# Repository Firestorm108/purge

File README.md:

# purge
**Purge** is a fully open source wireless inductively coupled plasma cleaner consisting of three isolated PCBs; the external user-control board, STM32 based motherboard, spark generator/ICP driver, and a vaccum chamber.

# PCB & Assembly

# The Process

**Purge** is a specialized type of plasma cleaner. There are **zero** electrodes in the vacuum chamber, meaning the sterility levels are very high, atomically sterile even. There are three stages to the process.

<h3>Stage 1: Chamber Prep</h3>
A 4.5 CFM standard vacuum pump evacuates much of the air inside of the glass dome to 37.5 mTorr. This makes the plasma much easier to form, as there is a reduced gas density. 
The chamber is made up of a custom machined aluminum base and a cheap glass dome you can find on Amazon. There is a slight implosion risk, so it is important you wear proper PPE.

<h3>Stage 2: Plasma Formation</h3>
There are two parts to the plasma formation. Since inductively coupled plasma (ICP) is relatively harder to form than capacitively coupled plasma or direct discharges, simply running the RF through the primary coil may not form the plasma.
To form the plasma, we initiate a short high voltage spark with an external device. In this case, I'm using a high frequency solid state plasma flame generator, similar to the ICP circuit itself. It ionizes some of the gas in the chamber, making
ICP form much easier. The ICP driver powers on after this, and the chamber fills with plasma.

<h3>Stage 3: Adjustment & Control</h3>
You can change the plasma inside the chamber using the built in STM32 interrupter. It allows you to pulse the plasma at any desired frequency within the chip and MOSFETs limits. This can be useful if you are trying to 
do research using the device, or wish to adjust power levels based on the item you are sterilizing.

# Bill of Materials

| Item | Price | Link |
|---|---:|---|
| Control PCB | $10 | JLCPCB |
| Header Pins | $3 | [AliExpress](https://www.aliexpress.us/item/3256801327743339.html) |
| OLED Screen | $4 | [AliExpress](https://www.aliexpress.us/item/3256805954920554.html) |
| 10K Potentiometers | $4 | [AliExpress](https://www.aliexpress.us/item/3256809938132755.html) |
| Push Button | $4 | [AliExpress](https://www.aliexpress.us/item/3256808590713102.html) |
| 3mm Flat Top LEDs | $2 | [AliExpress](https://www.aliexpress.us/item/2251801539552759.html) |
| F-F Jumpers | $2 | [AliExpress](https://www.aliexpress.us/item/2255800018543465.html) |
| ICP Driver PCB + Assembly | $55 | JLCPCB |
| FQA18N50 MOSFETs | $10 | [AliExpress](https://www.aliexpress.us/item/3256811881586105.html) |
| 6kV 33pF Capacitors | $2 | [AliExpress](https://www.aliexpress.us/item/2251832494176278.html) |
| 12AWG Solid Core | $4 | [AliExpress](https://www.aliexpress.us/item/3256808900976117.html) |
| Massive Heatsink | $10 | [AliExpress](https://www.aliexpress.us/item/3256809168389115.html) |
| HFSSTC Module | $24 | [AliExpress](https://www.aliexpress.us/item/3256810369157220.html) |
| 24AWG Solid Core (Inductor Wire) | $7 | [Amazon](https://www.amazon.com/0-2mm%C2%B2-Electrical-Colors-Tinned-breadboard/dp/B09WMQZYXV/) |
| 6AWG Primary Copper | $24 | [Amazon](https://www.amazon.com/99-9-Copper-Diameter-Jewelry-Making/dp/B0CNRT19WB/) |
| Purge Motherboard PCB + Assembly | $80 | JLCPCB |
| 24V → 12V Isolation SMPS | $6 | [AliExpress](https://www.aliexpress.us/item/3256807230654430.html) |
| 24V 10A Power Supply | $30 | [Amazon](https://www.amazon.com/Power-Supply-Adapter-Transformers-Universal/dp/B0D5B33JCH) |
| JLCPCB Customs & Shipping | $91 | JLCPCB |
| 4" × 7" Glass Dome | $30 | [Amazon](https://www.amazon.com/Plymor-Brand-Glass-Display-Cloche/dp/B006XIQGX8/) |
| 4.5 CFM Vacuum Pump | $60 | [Amazon](https://www.amazon.com/VECOTOOLS-Foldable-Automotive-Household-Maintenance/dp/B0GZVLP3PL/) |
| Hosing & Gauge | $28 | [Amazon](https://www.amazon.com/R410A-Recharge-Manifold-Gauge-Set/dp/B0DZ6G6ZBT/) |
| SAE to NPT Adapter | $9 | [Amazon](https://www.amazon.com/uxcell-Fitting-Connector-Conditioner-Refrigeration/dp/B08MZ4TPMZ/) |
| NPT Tap | $7 | [Amazon](https://www.amazon.com/Drill-America-DWTPT1-Qualtech-Carbon/dp/B01DZD1SSQ/) |
| M5 × 100mm Threaded Rods | $10 | [Amazon](https://www.amazon.com/LWCUSNJ-Threaded-M5-0-8mm-Stainless-Threads/dp/B0FHB8P689/) |
| Silicone Caulk | $3 | [Amazon](https://www.amazon.com/White-Acrylic-Latex-Caulk-Silicone/dp/B00GVLHBDG/) |
| Custom Aluminum Base Plate | $50 | JLC CNC |
| Silicone Isolation Feet | $20 | [Amazon](https://www.amazon.com/Isolation-Feet-8Pack-Turntable-Subwoofer-Resonance/dp/B0FX8S3D77) |

**Total: $589**

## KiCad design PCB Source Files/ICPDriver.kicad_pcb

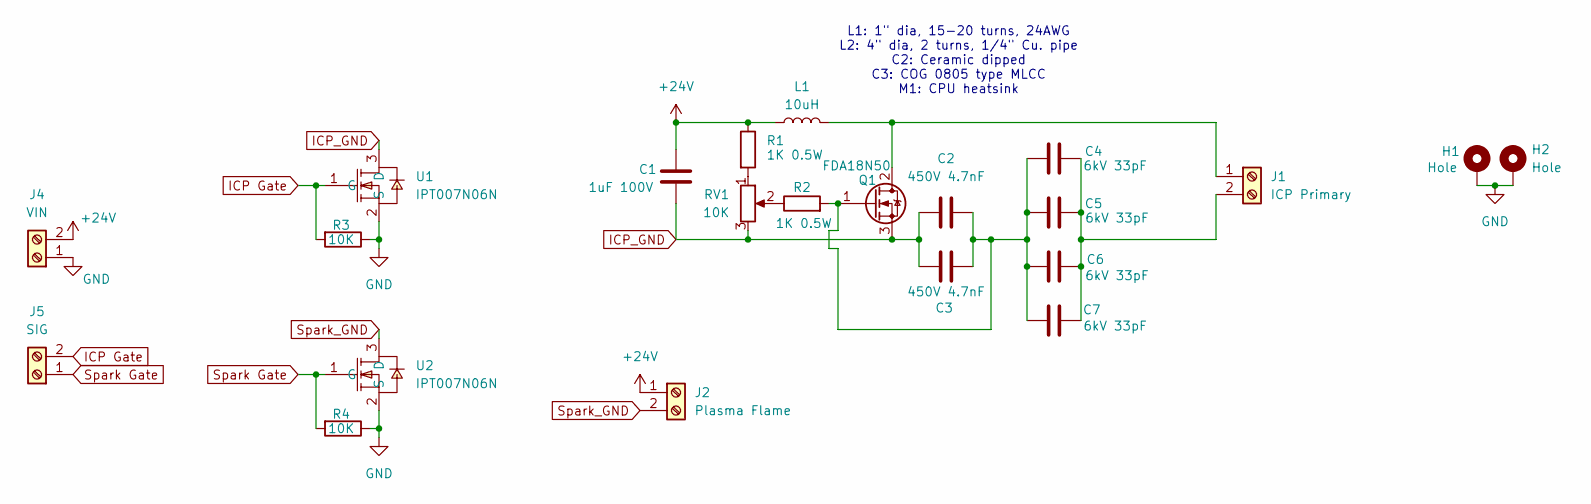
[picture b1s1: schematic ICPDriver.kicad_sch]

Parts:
C1: 1uF 100V; C_1206_3216Metric
C2, C3: 450V 4.7nF; C_1812_4532Metric
C4, C5, C6, C7: 6kV 33pF; C_Disc_D7.5mm_W5.0mm_P7.50mm
H1, H2: Hole; MountingHole_3.2mm_M3_Pad
J1: ICP Primary; CONN-TH_P10.16_KF135T-10.16-2P
J2: Plasma Flame; CONN-TH_P10.16_KF135T-10.16-2P
J4: VIN; CONN-TH_P10.16_KF135T-10.16-2P
J5: SIG; CONN-TH_P10.16_KF135T-10.16-2P
L1: 10uH; CONN-TH_P10.16_KF135T-10.16-2P
Q1: FDA18N50; TO-247-3_Vertical
R1, R2: 1K 0.5W; R_2512_6332Metric
R3, R4: 10K; R_0603_1608Metric
RV1: 10K; RES-ADJ-TH_RK1631110U1Q
U1, U2: IPT007N06N; HSOF-8_IPT007N06N; MPN IPT007N06N(TOKMAS); LCSC Part C19626228

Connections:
+24V: C1.1, J2.1, J4.2, L1.1, R1.1
GND: H1.1 (1_1), H2.1 (1_1), J4.1, R3.1, R4.1, U1.2 (S), U2.2 (S)
ICP Gate: J5.2, R3.2, U1.1 (G)
ICP_GND: C1.2, C2.1, C3.1, Q1.3 (S), RV1.3, U1.3 (D)
unnamed: J1.1, L1.2, Q1.2 (D)
unnamed: C4.2, C5.2, C6.2, C7.2, J1.2
unnamed: C2.2, C3.2, C4.1, C5.1, C6.1, C7.1, Q1.1 (G), R2.2
unnamed: R1.2, RV1.1
unnamed: R2.1, RV1.2
Spark Gate: J5.1, R4.2, U2.1 (G)
Spark_GND: J2.2, U2.3 (D)

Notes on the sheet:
L1: 1" dia, 15-20 turns, 24AWG L2: 4" dia, 2 turns, 1/4" Cu. pipe C2: Ceramic dipped C3: COG 0805 type MLCC M1: CPU heatsink

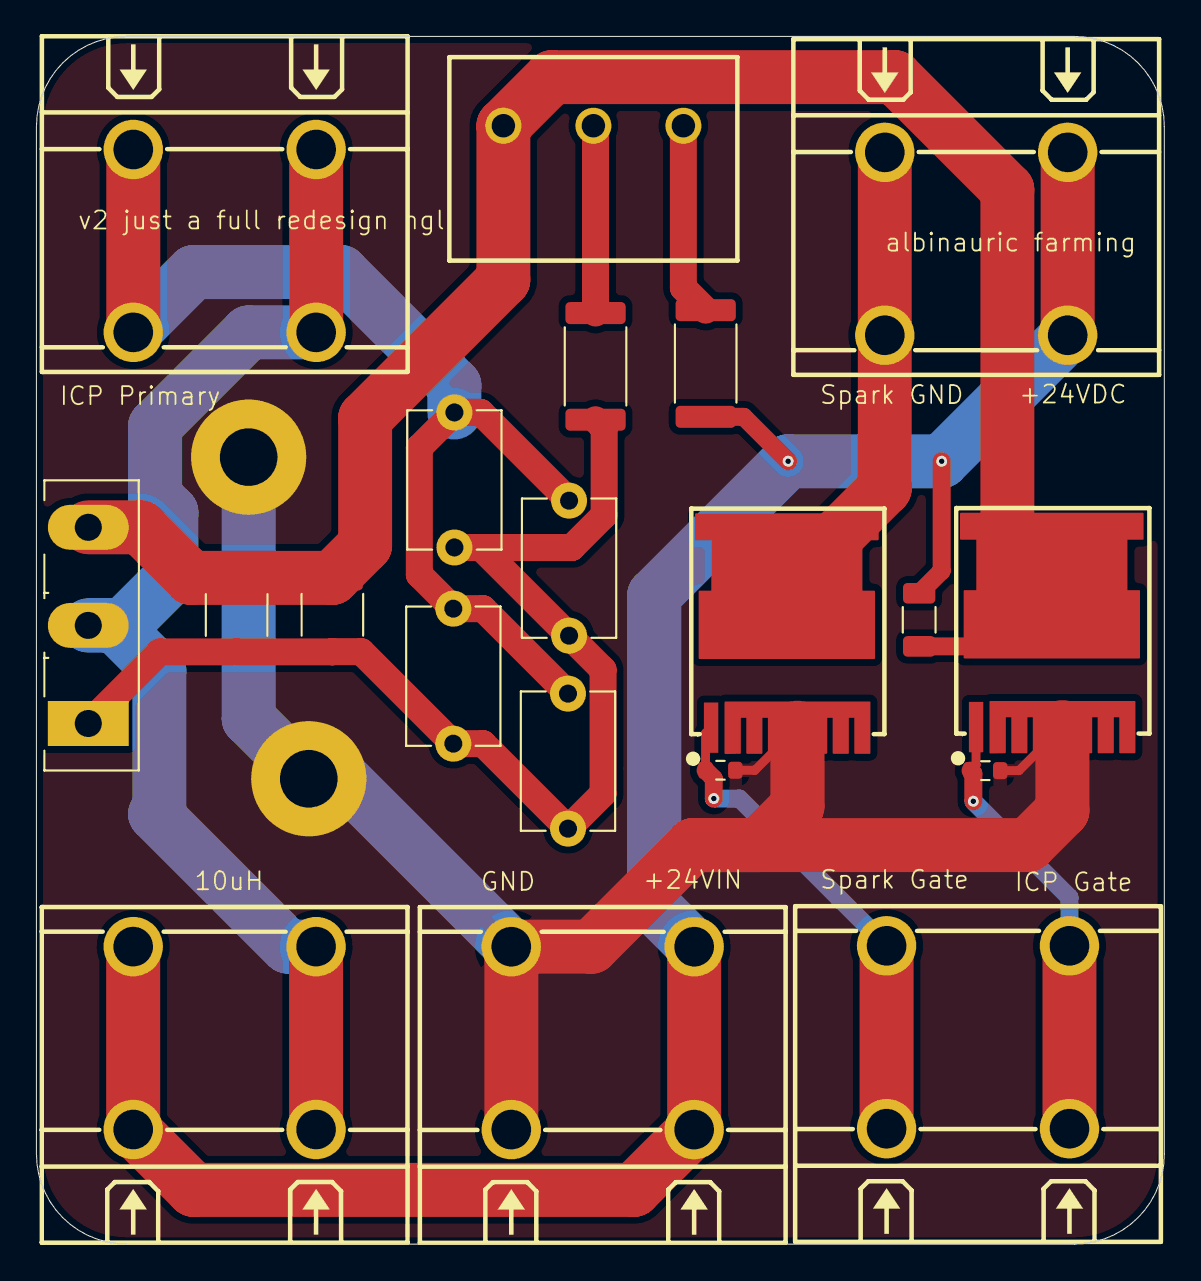
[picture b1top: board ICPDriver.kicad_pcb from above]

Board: 2 copper layers, 62.7 x 67.1 mm, 22 parts (0 on the bottom side), 11 nets.

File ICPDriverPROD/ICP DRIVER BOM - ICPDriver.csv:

Id,Designator,Footprint,Quantity,Comment,Supplier and ref
1,C1,C_1206_3216Metric,1,1uF 100V,
2,"C2, C3",C_1812_4532Metric,2,450V 4.7nF,
3,"C4, C5, C6, C7",C_Disc_D7.5mm_W5.0mm_P7.50mm,4,6kV 33pF,
4,J1,CONN-TH_P10.16_KF135T-10.16-2P,1,ICP Primary,
5,J2,CONN-TH_P10.16_KF135T-10.16-2P,1,Plasma Flame,
6,J4,CONN-TH_P10.16_KF135T-10.16-2P,1,VIN,
7,J5,CONN-TH_P10.16_KF135T-10.16-2P,1,SIG,
8,L1,CONN-TH_P10.16_KF135T-10.16-2P,1,10uH,
9,Q1,TO-247-3_Vertical,1,FDA18N50,
10,"R1, R2",R_2512_6332Metric,2,1K 0.5W,
11,"R3, R4",R_0603_1608Metric,2,10K,
12,RV1,RES-ADJ-TH_RK1631110U1Q,1,10K,
13,"U1, U2",HSOF-8_IPT007N06N,2,IPT007N06N,

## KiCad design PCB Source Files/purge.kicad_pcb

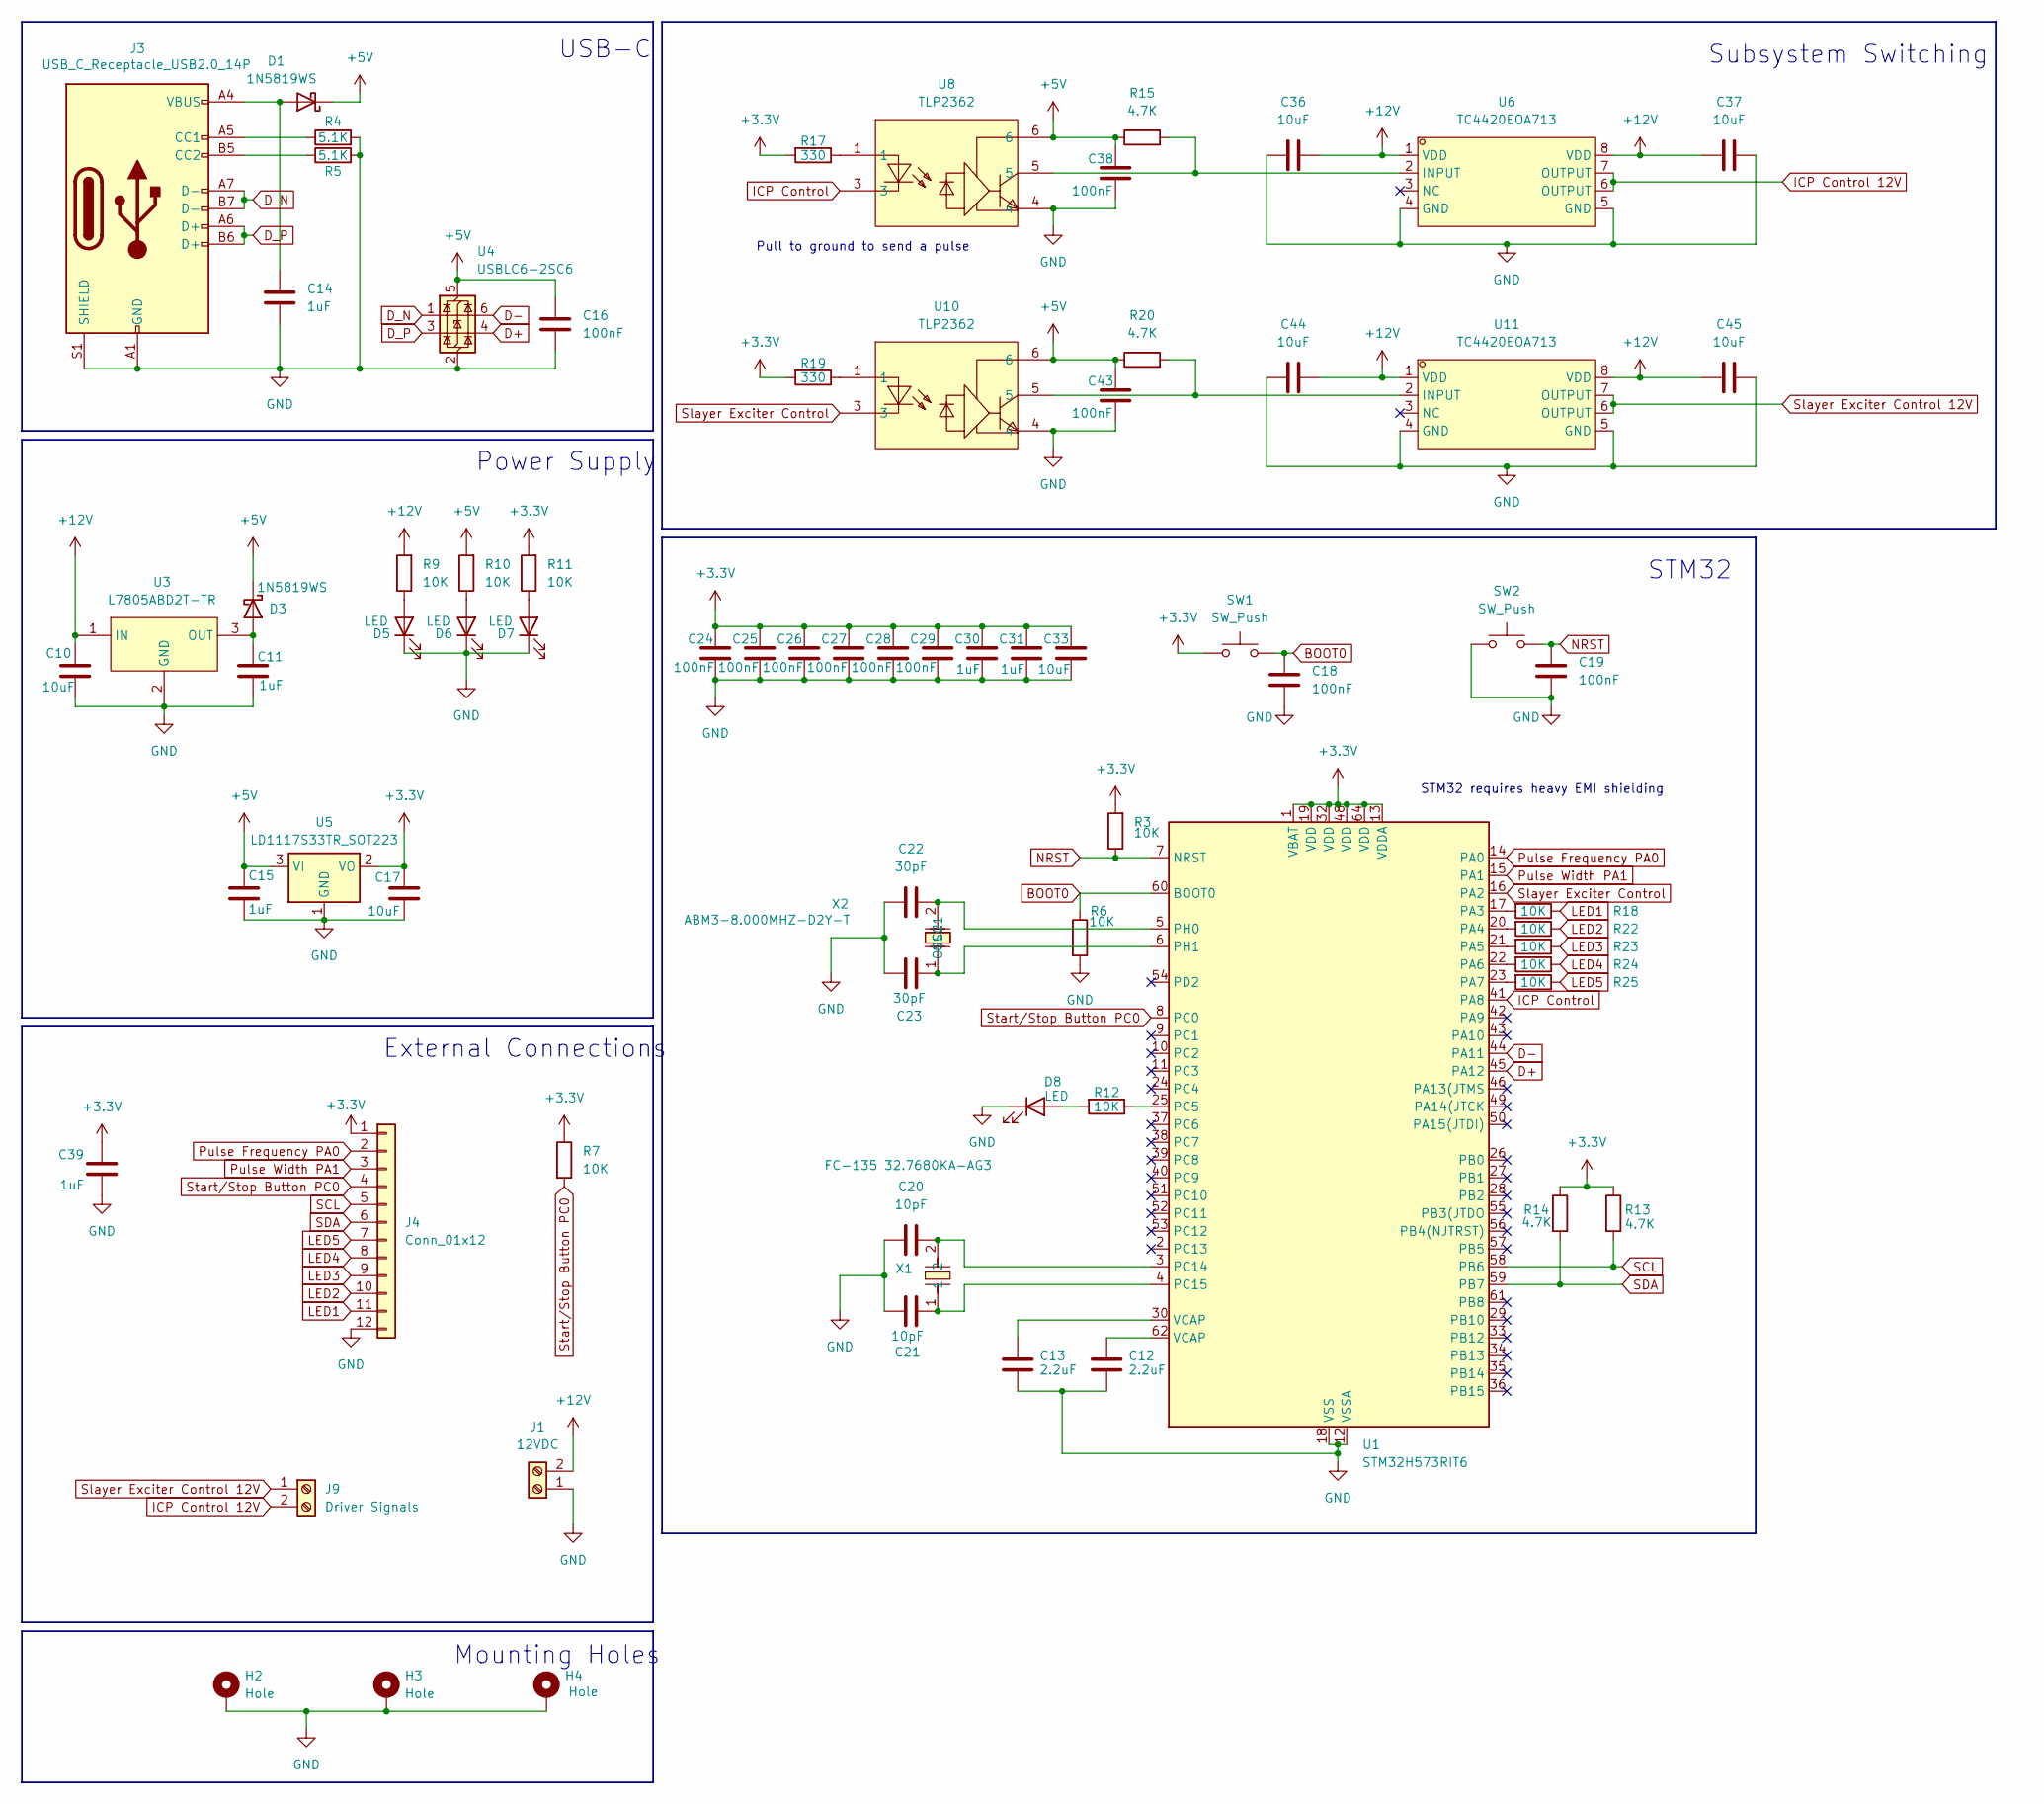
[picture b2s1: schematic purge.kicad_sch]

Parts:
C10, C17, C33, C36, C37, C44, C45: 10uF; C_0603_1608Metric
C11, C14, C15, C30, C31, C39: 1uF; C_0603_1608Metric
C12, C13: 2.2uF; C_0603_1608Metric
C16, C18, C19, C24, C25, C26, C27, C28, C29, C38, C43: 100nF; C_0402_1005Metric
C20, C21: 10pF; C_0402_1005Metric
C22, C23: 30pF; C_0402_1005Metric
D1, D3: 1N5819WS; D_SOD-323
D5, D6, D7, D8: LED; LED_0805_2012Metric
H2, H3, H4: Hole; MountingHole_3.2mm_M3_Pad
J1: 12VDC; CONN-TH_P10.16_KF135T-10.16-2P
J3: USB_C_Receptacle_USB2.0_14P; USB_C_Receptacle_HRO_TYPE-C-31-M-12
J4: Conn_01x12; PinHeader_1x12_P2.54mm_Vertical
J9: Driver Signals; CONN-TH_P10.16_KF135T-10.16-2P
R3, R6, R7, R9, R10, R11, R12, R18, R22, R23, R24, R25: 10K; R_0603_1608Metric
R4, R5: 5.1K; R_0603_1608Metric
R13, R14, R15, R20: 4.7K; R_0603_1608Metric
R17, R19: 330; R_0603_1608Metric
SW1, SW2: SW_Push; SW_Push_SPST_NO_Alps_SKRK
U1: STM32H573RIT6; LQFP-64_10x10mm_P0.5mm
U3: L7805ABD2T-TR; TO-263-2_L10.0-W9.2-P5.08-LS15.3-TL-CW; MPN L7805ABD2T-TR; LCSC Part C86206
U4: USBLC6-2SC6; SOT-23-6
U5: LD1117S33TR_SOT223; SOT-223-3_TabPin2
U6, U11: TC4420EOA713; SOIC-8_L5.0-W4.0-P1.27-LS6.0-BL; MPN TC4420EOA713; LCSC Part C231865
U8, U10: TLP2362; OPTO-SMD-5_L3.7-W4.6-P1.27-LS7.0-BR; MPN TLP2362(TPL,E; LCSC Part C37658
X1: FC-135 32.7680KA-AG3; CRYSTAL-SMD_L3.2-W1.5-1; MPN FC-135 32.7680KA-AG3; LCSC Part C7275970
X2: ABM3-8.000MHZ-D2Y-T; OSC-SMD_L5.0-W3.2; MPN ABM3-8.000MHZ-D2Y-T; LCSC Part C144380

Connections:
+3.3V: C17.1, C24.1, C25.1, C26.1, C27.1, C28.1, C29.1, C30.1, C31.1, C33.1, C39.1, J4.1, R3.2, R7.1, R11.2, R13.1, R14.1, R17.2, R19.2, SW1.1, U1.1 (VBAT), U1.13 (VDDA), U1.19 (VDD), U1.32 (VDD), U1.48 (VDD), U1.64 (VDD), U5.2 (VO)
+5V: C15.1, C16.1, C38.1, C43.1, D1.1 (K), D3.1 (K), R10.2, R15.1, R20.1, U4.5 (VBUS), U5.3 (VI), U8.6, U10.6
+12V: C10.1, C36.2, C37.1, C44.2, C45.1, J1.2, R9.2, U3.1 (IN), U6.1 (VDD), U6.8 (VDD), U11.1 (VDD), U11.8 (VDD)
BOOT0: C18.1, R6.1, SW1.2, U1.60 (BOOT0)
D+: U1.45 (PA12), U4.4 (I/O2)
D-: U1.44 (PA11), U4.6 (I/O1)
D_N: J3.A7 (D-), J3.B7 (D-), U4.1 (I/O1)
D_P: J3.A6 (D+), J3.B6 (D+), U4.3 (I/O2)
GND: C10.2, C11.2, C12.2, C13.2, C14.2, C15.2, C16.2, C17.2, C18.2, C19.2, C20.1, C21.1, C22.1, C23.1, C24.2, C25.2, C26.2, C27.2, C28.2, C29.2, C30.2, C31.2, C33.2, C36.1, C37.2, C38.2, C39.2, C43.2, C44.1, C45.2, D5.1 (K), D6.1 (K), D7.1 (K), D8.1 (K), H2.1 (1_1), H3.1 (1_1), H4.1 (1_1), J1.1, J3.A1 (GND), J3.A12 (GND), J3.B1 (GND), J3.B12 (GND), J3.S1 (SHIELD), J4.12, R4.2, R5.2, R6.2, SW2.1, U1.12 (VSSA), U1.18 (VSS), U1.31 (VSS), U1.47 (VSS), U1.63 (VSS), U3.2 (GND), U4.2 (GND), U5.1 (GND), U6.4 (GND), U6.5 (GND), U8.4, U10.4, U11.4 (GND), U11.5 (GND)
ICP Control: U1.41 (PA8), U8.3
ICP Control 12V: J9.2, U6.6 (OUTPUT), U6.7 (OUTPUT)
LED1: J4.11, R18.1
LED2: J4.10, R22.1
LED3: J4.9, R23.1
LED4: J4.8, R24.1
LED5: J4.7, R25.1
NRST: C19.1, R3.1, SW2.2, U1.7 (NRST)
unnamed: C12.1, U1.62 (VCAP)
unnamed: C13.1, U1.30 (VCAP)
unnamed: C14.1, D1.2 (A), J3.A4 (VBUS), J3.A9 (VBUS), J3.B4 (VBUS), J3.B9 (VBUS)
unnamed: C11.1, D3.2 (A), U3.3 (OUT)
unnamed: D5.2 (A), R9.1
unnamed: D6.2 (A), R10.1
unnamed: D7.2 (A), R11.1
unnamed: D8.2 (A), R12.2
unnamed: J3.A5 (CC1), R4.1
unnamed: J3.B5 (CC2), R5.1
unnamed: R17.1, U8.1
unnamed: R19.1, U10.1
unnamed: R18.2, U1.17 (PA3)
unnamed: R22.2, U1.20 (PA4)
unnamed: R23.2, U1.21 (PA5)
unnamed: R24.2, U1.22 (PA6)
unnamed: R25.2, U1.23 (PA7)
unnamed: R12.1, U1.25 (PC5)
unnamed: C20.2, U1.3 (PC14), X1.2
unnamed: C21.2, U1.4 (PC15), X1.1
unnamed: C22.2, U1.5 (PH0), X2.2 (OSC2)
unnamed: C23.2, U1.6 (PH1), X2.1 (OSC1)
unnamed: R15.2, U6.2 (INPUT), U8.5
unnamed: R20.2, U10.5, U11.2 (INPUT)
Pulse Frequency PA0: J4.2, U1.14 (PA0)
Pulse Width PA1: J4.3, U1.15 (PA1)
SCL: J4.5, R13.2, U1.58 (PB6)
SDA: J4.6, R14.2, U1.59 (PB7)
Slayer Exciter Control: U1.16 (PA2), U10.3
Slayer Exciter Control 12V: J9.1, U11.6 (OUTPUT), U11.7 (OUTPUT)
Start/Stop Button PC0: J4.4, R7.2, U1.8 (PC0)

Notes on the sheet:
USB-C
External Connections
Subsystem Switching
Mounting Holes
Power Supply
STM32 requires heavy EMI shielding
STM32
Pull to ground to send a pulse

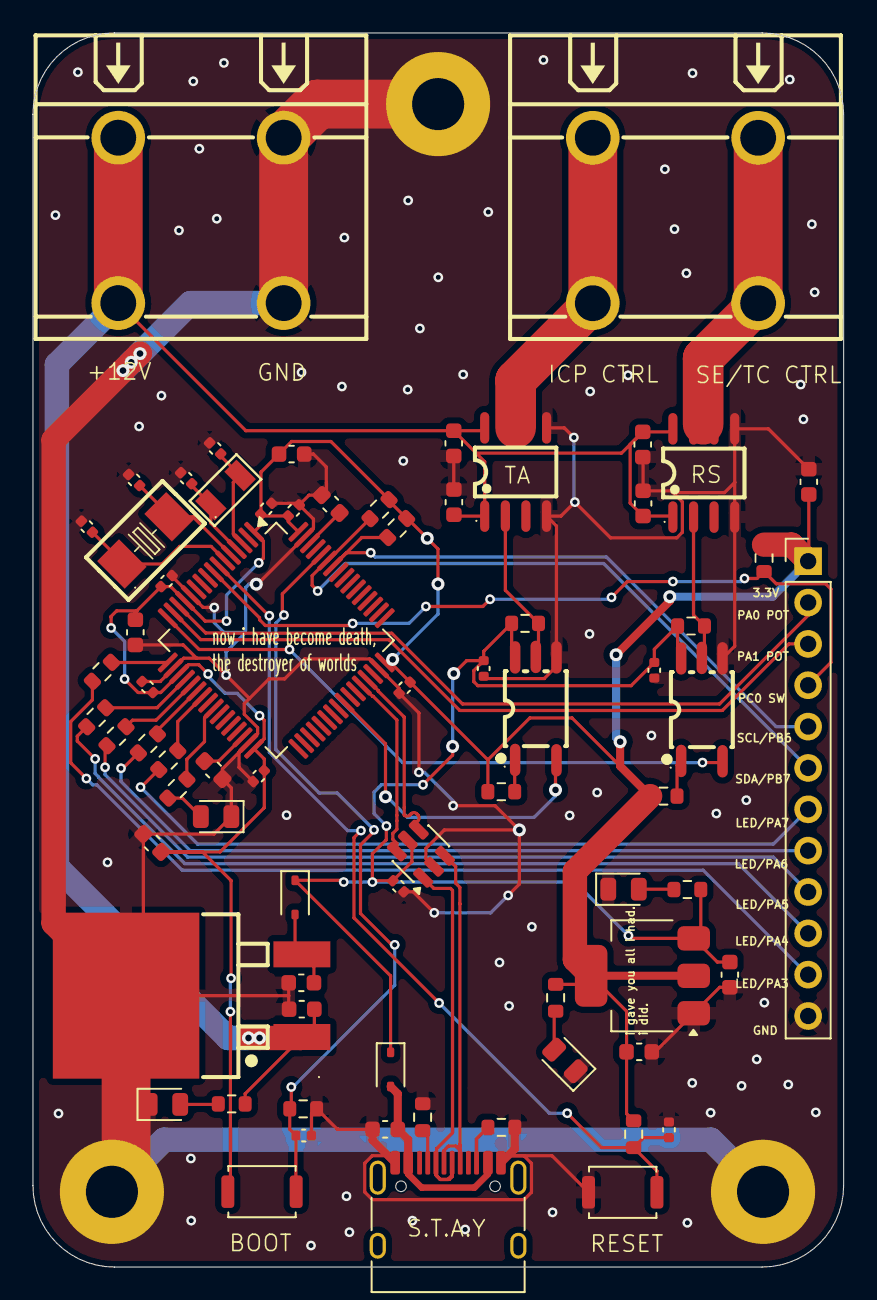
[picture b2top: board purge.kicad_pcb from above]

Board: 2 copper layers, 49.8 x 75.8 mm, 75 parts (0 on the bottom side), 48 nets.

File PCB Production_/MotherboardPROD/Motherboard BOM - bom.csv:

Id,Designator,Footprint,Quantity,Comment,Supplier and ref
1,"C10, C17, C33, C36, C37, C44, C45",C_0603_1608Metric,7,10uF,
2,"C11, C14, C15, C30, C31, C39",C_0603_1608Metric,6,1uF,
3,"C12, C13",C_0603_1608Metric,2,2.2uF,
4,"C16, C18, C19, C24, C25, C26, C27, C28, C29, C38, C43",C_0402_1005Metric,11,100nF,
5,"C20, C21",C_0402_1005Metric,2,10pF,
6,"C22, C23",C_0402_1005Metric,2,30pF,
7,"D1, D3",D_SOD-323,2,1N5819WS,
8,"D5, D6, D7, D8",LED_0805_2012Metric,4,LED,
9,J1,CONN-TH_P10.16_KF135T-10.16-2P,1,12VDC,
10,J3,USB_C_Receptacle_HRO_TYPE-C-31-M-12,1,USB_C_Receptacle_USB2.0_14P,
11,J4,PinHeader_1x12_P2.54mm_Vertical,1,Conn_01x12,
12,J9,CONN-TH_P10.16_KF135T-10.16-2P,1,Driver Signals,
13,"R3, R6, R7, R9, R10, R11, R12, R18, R22, R23, R24, R25",R_0603_1608Metric,12,10K,
14,"R4, R5",R_0603_1608Metric,2,5.1K,
15,"R13, R14, R15, R20",R_0603_1608Metric,4,4.7K,
16,"R17, R19",R_0603_1608Metric,2,330,
17,"SW1, SW2",SW_Push_SPST_NO_Alps_SKRK,2,SW_Push,
18,U1,LQFP-64_10x10mm_P0.5mm,1,STM32H573RIT6,
19,U3,TO-263-2_L10.0-W9.2-P5.08-LS15.3-TL-CW,1,L7805ABD2T-TR,
20,U4,SOT-23-6,1,USBLC6-2SC6,
21,U5,SOT-223-3_TabPin2,1,LD1117S33TR_SOT223,
22,"U6, U11",SOIC-8_L5.0-W4.0-P1.27-LS6.0-BL,2,TC4420EOA713,
23,"U8, U10",OPTO-SMD-5_L3.7-W4.6-P1.27-LS7.0-BR,2,TLP2362,
24,X1,CRYSTAL-SMD_L3.2-W1.5-1,1,FC-135 32.7680KA-AG3,
25,X2,OSC-SMD_L5.0-W3.2,1,ABM3-8.000MHZ-D2Y-T,

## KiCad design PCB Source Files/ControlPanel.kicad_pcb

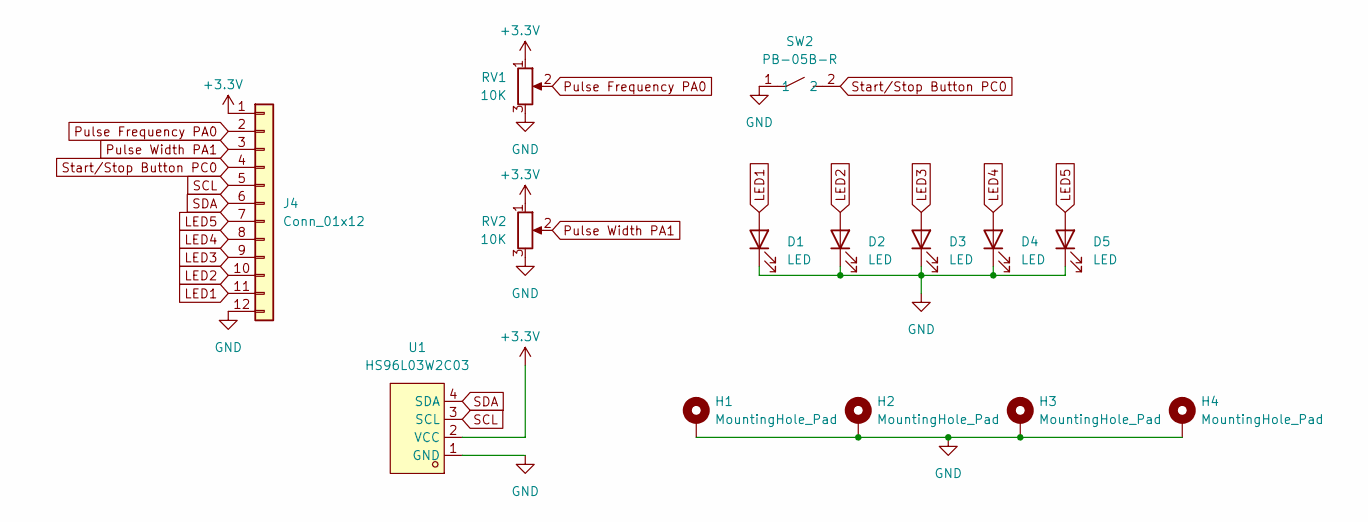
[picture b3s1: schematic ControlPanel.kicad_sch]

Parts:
D1, D2, D3, D4, D5: LED; LED_D3.0mm
H1, H2, H3, H4: MountingHole_Pad; MountingHole_3.2mm_M3_Pad
J4: Conn_01x12; PinHeader_1x12_P2.54mm_Vertical
RV1, RV2: 10K; Potentiometer_Alps_RK163_Single_Horizontal
SW2: PB-05B-R; CONN-TH_PB-05B-R; MPN PB-05B-R; LCSC Part C268254
U1: HS96L03W2C03; OLED-TH_L27.8-W27.2-P2.54_C9900033791; MPN HS96L03W2C03; LCSC Part C5248080

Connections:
+3.3V: J4.1, RV1.1, RV2.1, U1.2 (VCC)
GND: D1.1 (K), D2.1 (K), D3.1 (K), D4.1 (K), D5.1 (K), H1.1 (1_1), H2.1 (1_1), H3.1 (1_1), H4.1 (1_1), J4.12, RV1.3, RV2.3, SW2.1, U1.1 (GND)
LED1: D1.2 (A), J4.11
LED2: D2.2 (A), J4.10
LED3: D3.2 (A), J4.9
LED4: D4.2 (A), J4.8
LED5: D5.2 (A), J4.7
Pulse Frequency PA0: J4.2, RV1.2
Pulse Width PA1: J4.3, RV2.2
SCL: J4.5, U1.3 (SCL)
SDA: J4.6, U1.4 (SDA)
Start/Stop Button PC0: J4.4, SW2.2

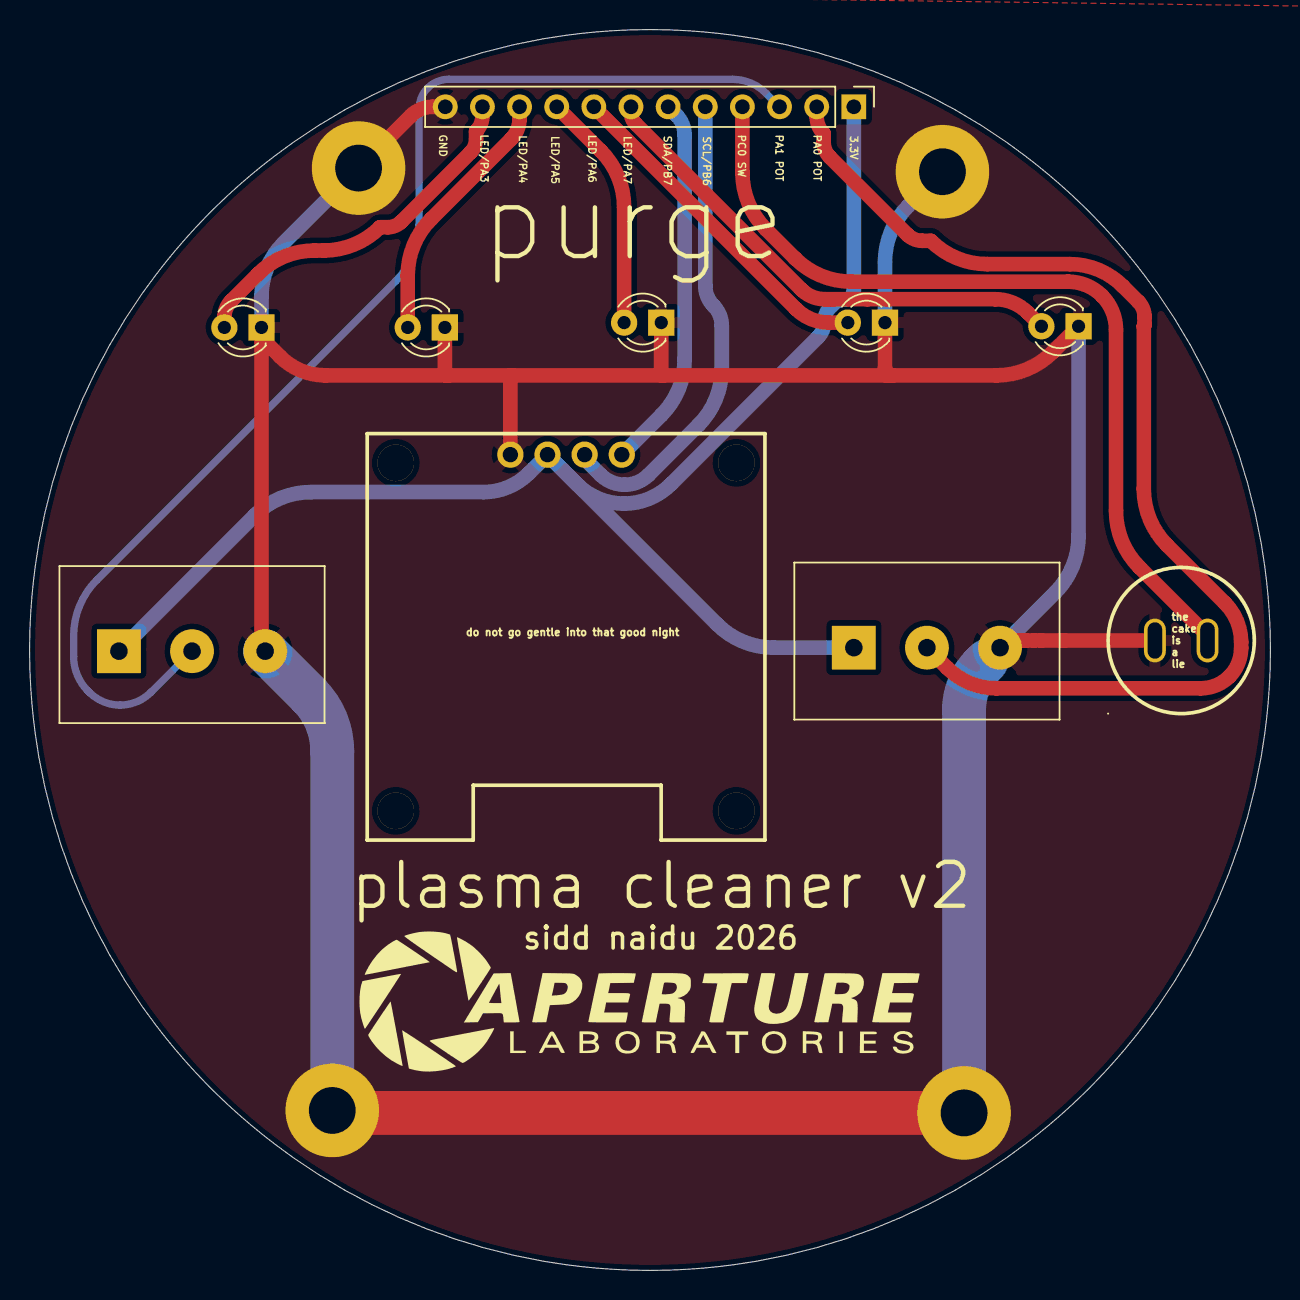
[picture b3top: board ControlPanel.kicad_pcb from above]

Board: 2 copper layers, 84.9 x 84.9 mm, 14 parts (0 on the bottom side), 12 nets.
